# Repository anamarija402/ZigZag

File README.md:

## RadionaOrg ZigZag badge

### Request and starting point

We got request from BSidesZG to design some blink LED badge with some interesting task to solve.

https://www.bsideszagreb.com/

As badge may slightly change over time here is aditional README for BSidesZG

Starting point for our badge was RVPC from Olimex, we have preserved most of schematics, and added LEDs

The EURO 1.00 Risc-V personal computer with VGA and Keyboard and Woz like monitor. The purpose of this project is to make educational platform which people can use to learn RISCV assembler and experiment like in the old days in 1980s :)

https://www.olimex.com/Products/Retro-Computers/RVPC/open-source-hardware

We whare also inspired with BalCCon badge that is using same chip.

https://2k25.balccon.org/

### Few of ideas we wanted to test

- [x] Keep it simple
- [x] Keep it low cost
- [x] Should solderable by hand
- [x] Input and outputs are needed
- [x] Tasks can be quickly changed added
- [x] It needs to be cheap to order assembled
- [x] Use most standard COIN CELL battery CR2032
- [x] Unique design that is connected to Radiona (ZigZag)
- [x] Badge should not draing to much current so it can survive conference day

### Why 5 LEDs?

With less then 5 LEDs we could do blinky, but with 5 we can do PoV

As we have BLUE and RED team, we have tested BLUE and RED LEDs.

RED LED are consuming less, and morse is better readable.

### Why Only one button?

We only have 6 pins, and we did not want to intraduce any aditinal chip.

And there are many things we can do with one button.

Considerring that we can have short press, long press, longer press, double press, tripple press - you get the point that one button should be enough for everything...

### Why those component and why 0603

We are using 0603 resistors and 0805 LEDs as they are still hand solderable, and we are using those on ULX3S so we can recycle components from scraped boards...

### Assembly

We wanted to confirm hand assembly, and low batch DIY assembly so we did first badge by hand, and rest of 69 badges with stencil. 
We baked first batch in oven but also checked paper stancil + hot air, and all works fine.

Paper is just 80g color paper. Diode laser cuts some colors better so we are using orange one.

For PCB holder we are using cuted cardboard

And for BOTTOM side we are using standoff cutter from hammer paper.

Applying paste to front side

### Implemented features

- [x] Fancy raider blinking
- [x] Morse used for output messages
- [x] PoV used for clues and solutions
- [x] Short button press
- [x] Long button press
- [ ] Other types of button presses
- [x] Sleep mode
- [ ] Deep sleep mode

### Make it hackable!

We did not want to remove any RVPC component so with moving few resistors and closing jumpers you could even have RVPC with VGA, PS2 and speaker...

### Badge software

https://github.com/RadionaOrg/ZigZag/tree/main/SOFTWARE/PlatformIO/ZigZag

We are using VScode + PlatformIO for building and flash.sh for flashing...

### Programming

We are using raspberry pico and this software for programming https://github.com/aappleby/picorvd 

Be warned not to remove initial 5 sec delay if you want to keep badge programmable with picorvd.

For programming you only need GND and PD6 test point.

### Test points

### Schematic

### Licensee
* Hardware is released under CERN Open Hardware Licence Version 2 - Strongly Reciprocal
* Software is released under GPL V3 Licensee
* Documentation is released under CC BY-SA 4.0

Top side PCB design by Damir Prizmić
Back side PCB design by Goran Mahovlić

Idea: BSidesZG, Ante Jurjević, Damir Prizmić, Goran Mahovlić, kost, 1g0r, BalCCon Badge, Olimex RVPC

Code:  Goran Mahovlić 

Big thanks to Olimex for all RVPC code examples...

### Events

| Event  | No. of badges | Offered Solutions | Accepted solutions |
| ------ | ------------- | ----------------- | ------------------ |
| BSidesZG | 70 | 1 | 1 |

### Badge solvers

| Event  | Date | Name | Needed time |
| ------ | ------------- | ----------------- |-----|
| BSidesZG | 07.03.2025. | Jurica Radović |~4h |

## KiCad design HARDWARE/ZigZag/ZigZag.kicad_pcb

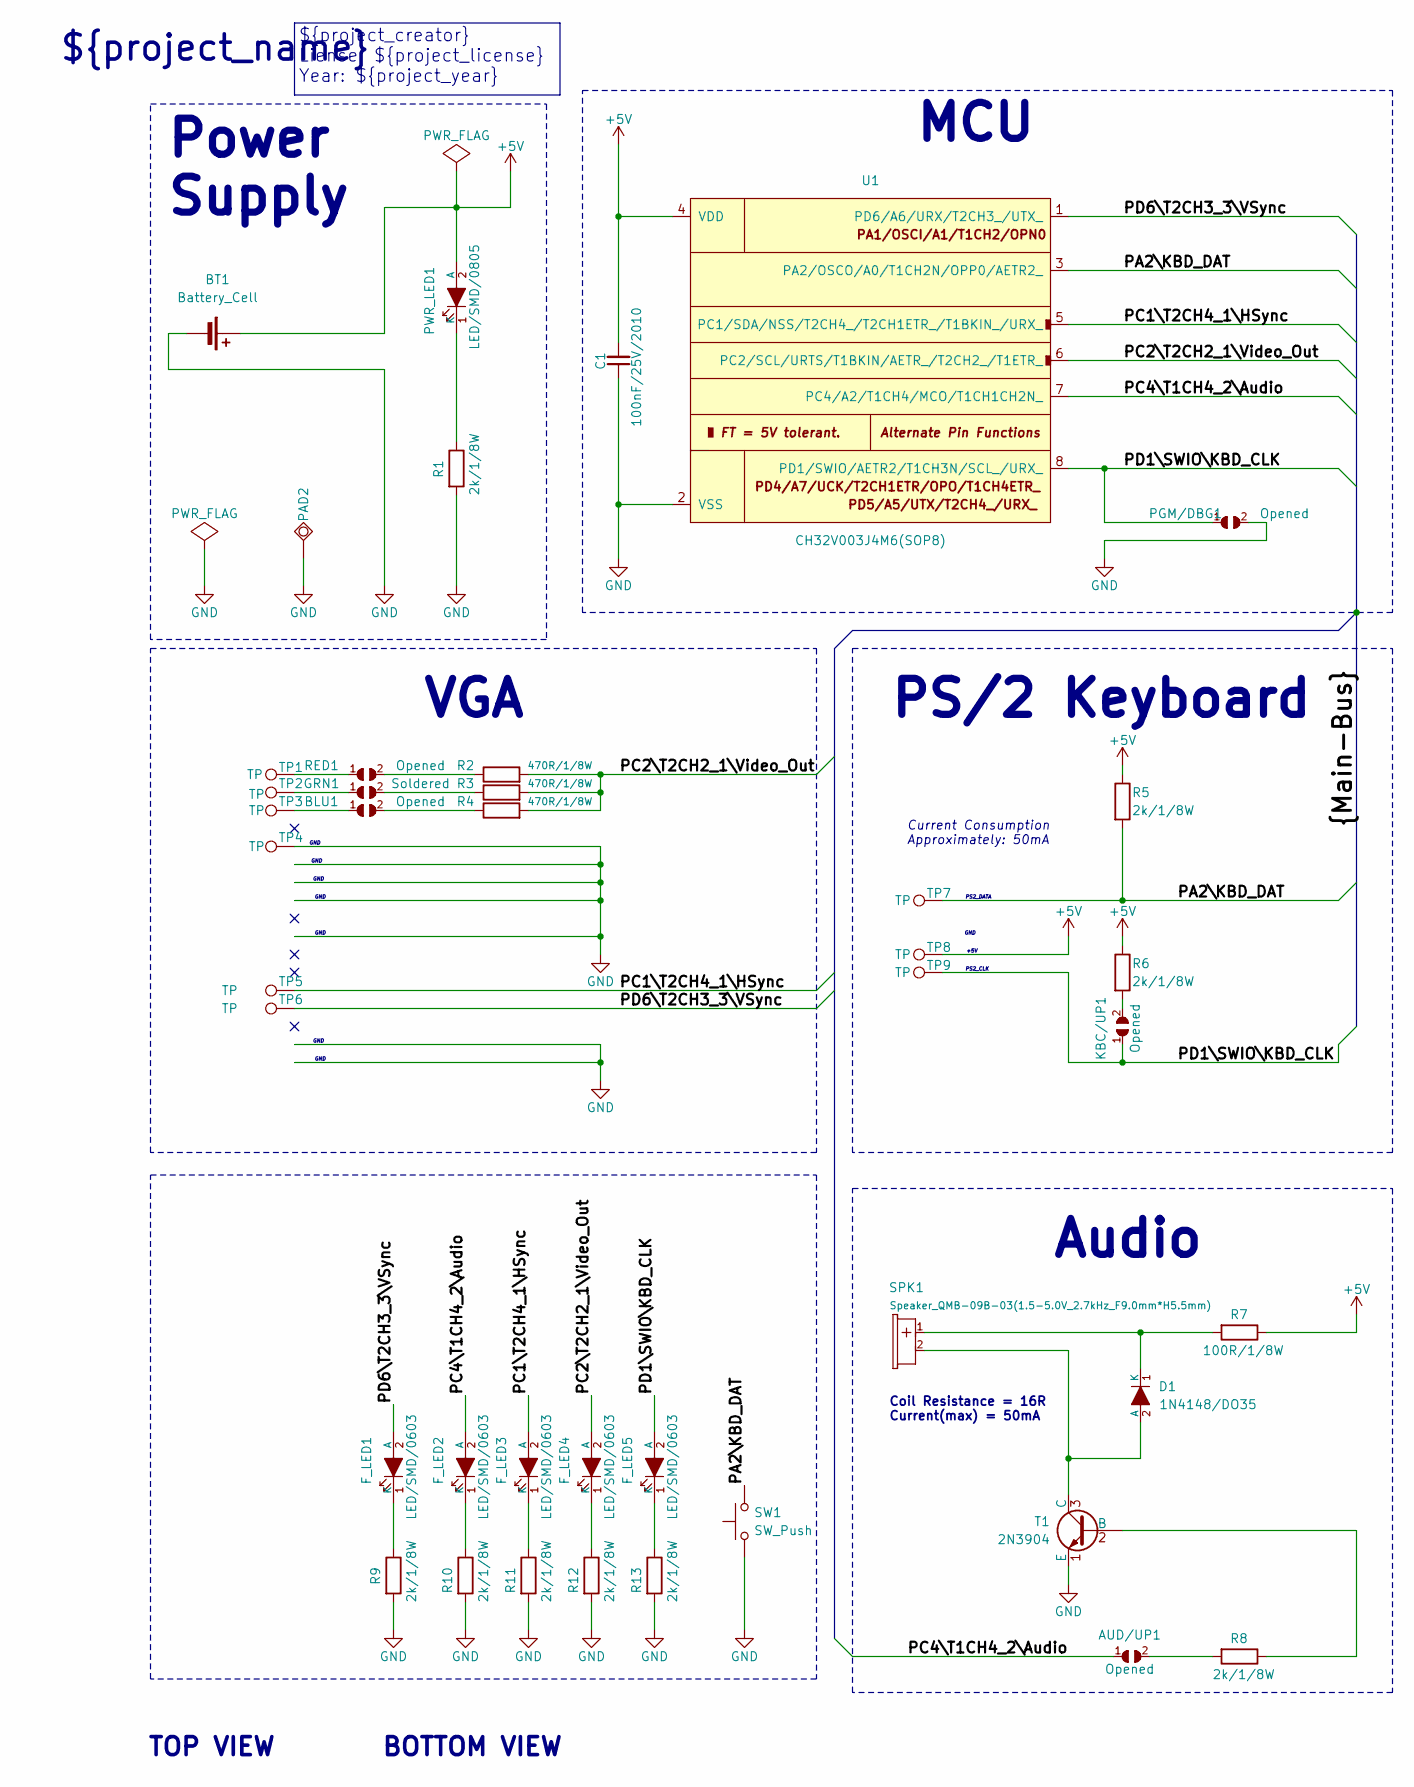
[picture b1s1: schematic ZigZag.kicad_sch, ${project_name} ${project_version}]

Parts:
AUD/UP1: Opened; SJ_1_SMALLER
BLU1: Opened; SJ_1_SMALLER
BT1: Battery_Cell; BatteryHolder_Keystone_3002_1x2032
C1: 100nF/25V/2010; C_0805_5MIL_DWS
D1: 1N4148/DO35; D_SOD-123
F_LED1, F_LED2, F_LED3, F_LED4, F_LED5: LED/SMD/0603; LED_0805_2012Metric_Pad1.15x1.40mm_HandSolder
GRN1: Soldered; SJ_1_SMALLER
KBC/UP1: Opened; SJ_1_SMALLER
PAD2: TESTPAD; arc_90_0.5
PGM/DBG1: Opened; SJ_1_SMALLER
PWR_LED1: LED/SMD/0805; LED_0805_2012Metric_Pad1.15x1.40mm_HandSolder
R1, R5, R6, R8, R9, R10, R11, R12, R13: 2k/1/8W; R_0603_1608Metric
R2, R3, R4: 470R/1/8W; R_0603_1608Metric
R7: 100R/1/8W; R_0603_1608Metric
RED1: Opened; SJ_1_SMALLER
SPK1: Speaker_QMB-09B-03(1.5-5.0V_2.7kHz_F9.0mm*H5.5mm); MagneticBuzzer_PUI_SMT-1028-T-2-R
SW1: SW_Push; SW_SPST_PTS645
T1: 2N3904; SOT-23
TP1, TP2, TP3, TP4, TP5, TP6, TP7, TP8, TP9: TP; TestPoint_Pad_D1.0mm
U1: CH32V003J4M6(SOP8); SOIC-8_150mil

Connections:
+5V: BT1.1 (+), C1.2, PWR_LED1.2 (A), R5.1, R6.1, R7.1, TP8.1, U1.4 (VDD)
/PA2\KBD_DAT: R5.2, SW1.2, TP7.1, U1.3 (PA2/OSCO/A0/T1CH2N/OPP0/AETR2_)
/PC1\T2CH4_1\HSync: F_LED3.2 (A), TP5.1, U1.5 (PC1/SDA/NSS/T2CH4_/T2CH1ETR_/T1BKIN_/UR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)
/PC2\T2CH2_1\Video_Out: F_LED4.2 (A), R2.2, R3.2, R4.2, U1.6 (PC2/SCL/URTS/T1BKIN/AETR_/T2CH2_/T1ETR_)
/PC4\T1CH4_2\Audio: AUD/UP1.1, F_LED2.2 (A), U1.7 (PC4/A2/T1CH4/MCO/T1CH1CH2N_)
/PD1\SWIO\KBD_CLK: F_LED5.2 (A), KBC/UP1.1, PGM/DBG1.1, TP9.1, U1.8 (PD1/SWIO/AETR2/T1CH3N/SCL_/URX_)
/PD6\T2CH3_3\VSync: F_LED1.2 (A), TP6.1, U1.1 (PD6/A6/URX/T2CH3_/UTX_)
GND: BT1.2 (-), C1.1, PAD2.1 (Pad), PGM/DBG1.2, R1.2, R9.2, R10.2, R11.2, R12.2, R13.2, SW1.1, T1.1 (E), TP4.1, U1.2 (VSS)
unnamed: AUD/UP1.2, R8.2
unnamed: BLU1.1, TP3.1
unnamed: BLU1.2, R4.1
unnamed: D1.2 (A), SPK1.2 (MINUS), T1.3 (C)
unnamed: D1.1 (K), R7.2, SPK1.1 (PLUS)
unnamed: F_LED1.1 (K), R9.1
unnamed: F_LED2.1 (K), R10.1
unnamed: F_LED3.1 (K), R11.1
unnamed: F_LED4.1 (K), R12.1
unnamed: F_LED5.1 (K), R13.1
unnamed: GRN1.1, TP2.1
unnamed: GRN1.2, R3.1
unnamed: KBC/UP1.2, R6.2
unnamed: PWR_LED1.1 (K), R1.1
unnamed: R2.1, RED1.2
unnamed: RED1.1, TP1.1
unnamed: R8.1, T1.2 (B)

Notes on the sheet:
Power Supply
${project_name}
GND
PS/2 Keyboard
PS2_CLK
BOTTOM VIEW
TOP VIEW
Current Consumption Approximately: 50mA
${project_creator} Liense: ${project_license} Year: ${project_year}
MCU
+5V
PS2_DATA
VGA
Audio
Coil Resistance = 16R Current(max) = 50mA

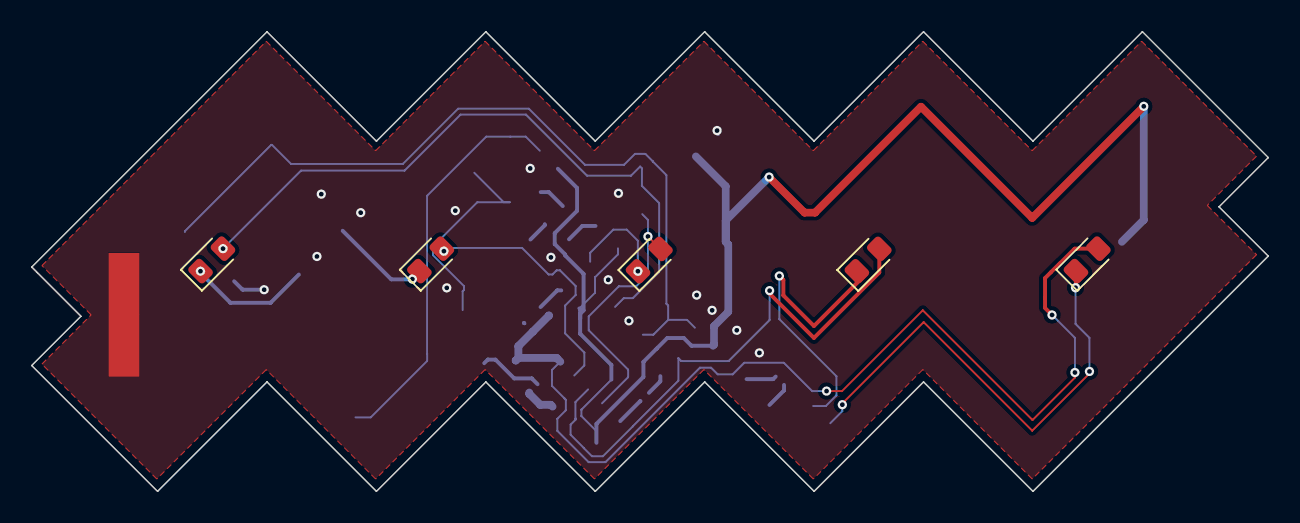
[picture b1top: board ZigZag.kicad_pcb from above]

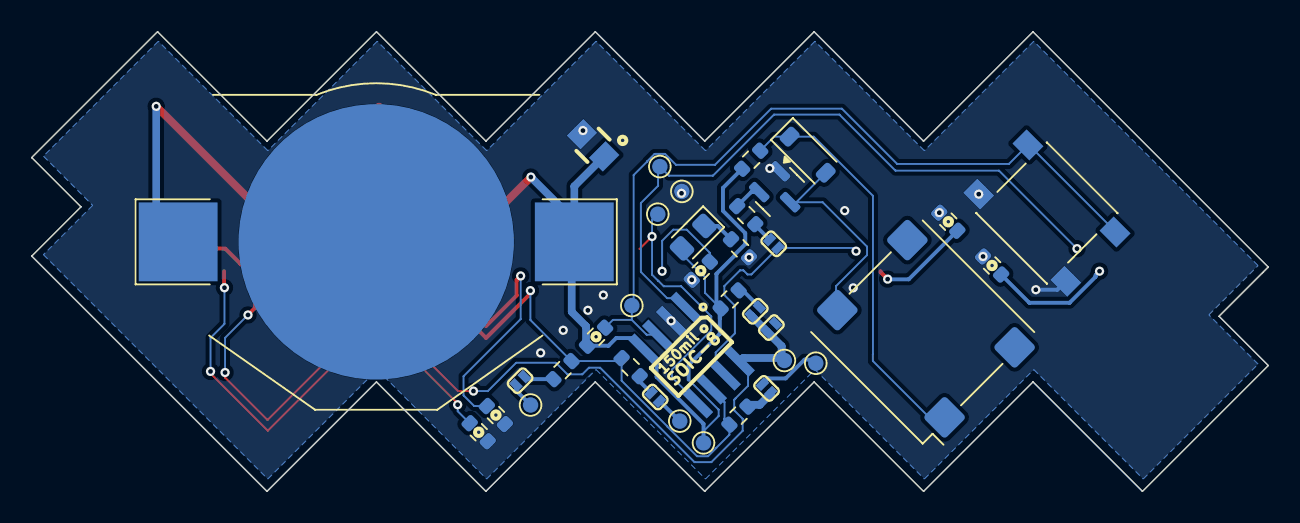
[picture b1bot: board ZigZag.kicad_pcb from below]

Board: 2 copper layers, 79.9 x 29.7 mm, 42 parts (36 on the bottom side), 25 nets.

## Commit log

2025-03-01 Removing RVPC - adding ZigZag
2025-03-02 Fixing D6 - Adding long press
2025-03-02 Adding Sleep on long press - place holder for deep sleep
2025-03-04 Adding BsidesZg folder
2025-03-04 New picture
2025-03-06 README
2025-03-07 README update
2025-03-08 Adding badbe solver
2025-03-08 Updating README
2025-03-08 Adding schematics
2025-03-08 Update picture
2025-03-09 CleanUP
2025-04-11 uređena schema
2025-04-15 dodan pdf
2025-04-24 Sync SCH and PCB
